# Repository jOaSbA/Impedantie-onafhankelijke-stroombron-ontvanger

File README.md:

"# Impedantie-onafhankelijke-stroombron-ontvanger"

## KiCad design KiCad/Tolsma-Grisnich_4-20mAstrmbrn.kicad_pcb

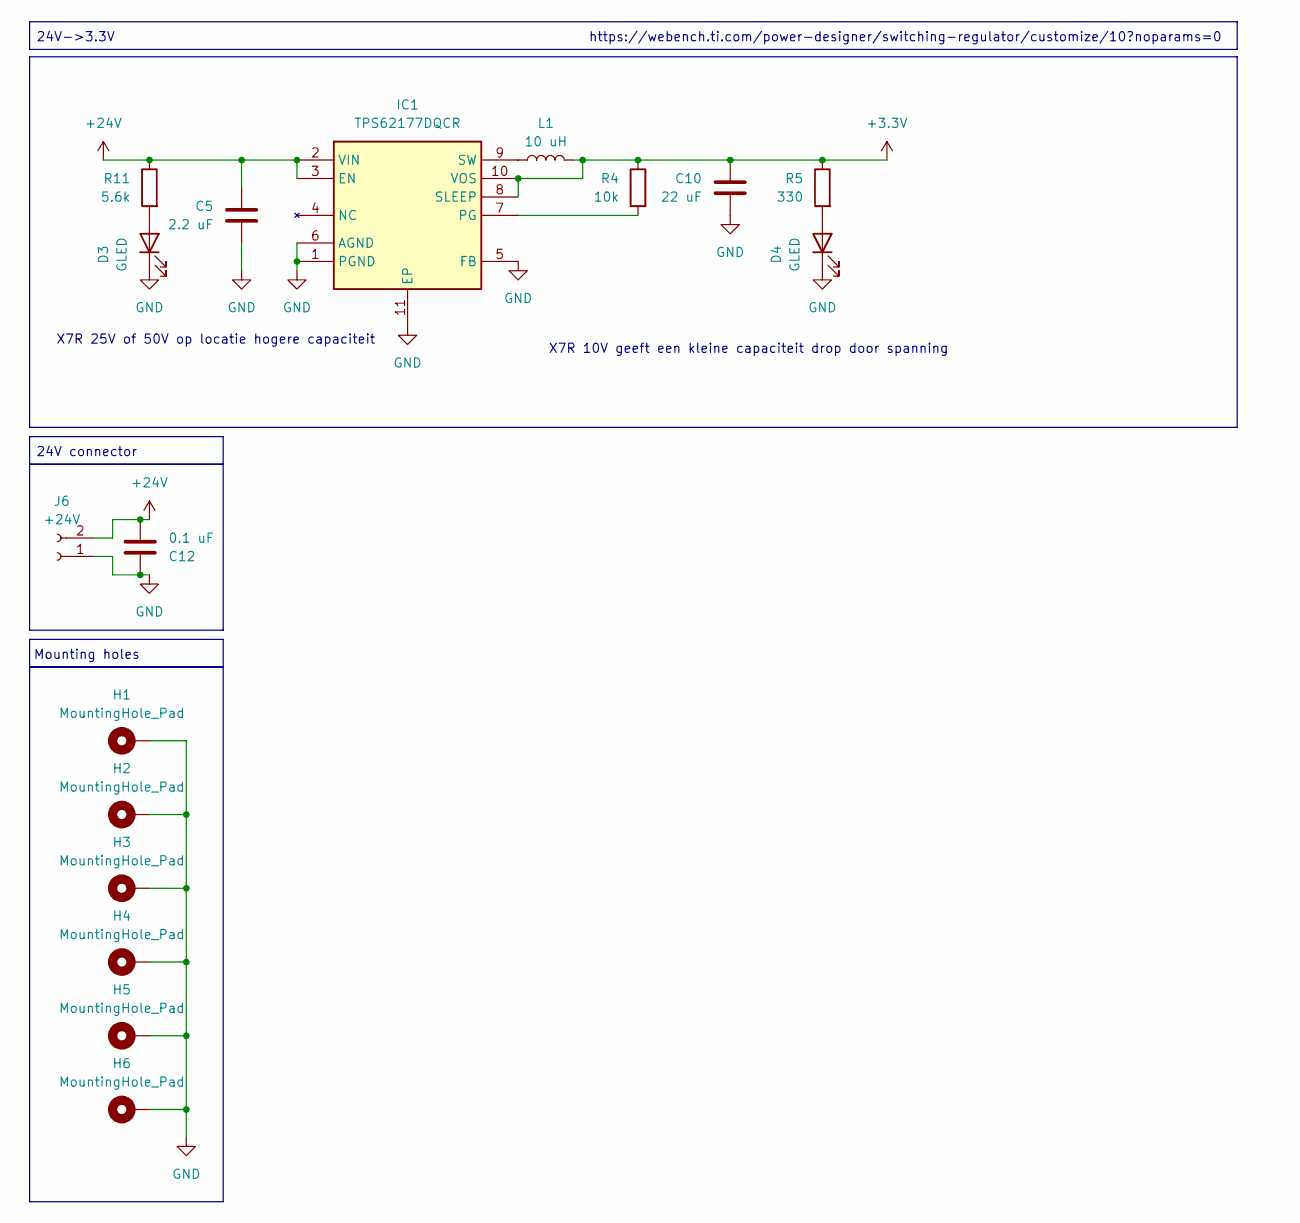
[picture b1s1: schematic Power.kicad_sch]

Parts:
C5: 2.2 uF; C_1206_3216Metric_Pad1.33x1.80mm_HandSolder
C10: 22 uF; C_1206_3216Metric_Pad1.33x1.80mm_HandSolder
C12: 0.1 uF; C_1206_3216Metric_Pad1.33x1.80mm_HandSolder
D3, D4: GLED; LED_0805_2012Metric_Pad1.15x1.40mm_HandSolder
H1, H2, H3, H4, H5, H6: MountingHole_Pad; MountingHole_3.2mm_M3_DIN965_Pad
IC1: TPS62177DQCR; SON50P200X300X80-11N; Mouser Part Number 595-TPS62177DQCR
J6: +24V; TerminalBlock_Xinya_XY308-2.54-2P_1x02_P2.54mm_Horizontal
L1: 10 uH; L_Wuerth_MAPI-3015
R4: 10k; R_1206_3216Metric_Pad1.30x1.75mm_HandSolder
R5: 330; R_1206_3216Metric_Pad1.30x1.75mm_HandSolder
R11: 5.6k; R_1206_3216Metric_Pad1.30x1.75mm_HandSolder

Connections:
+3.3V: C10.1, IC1.8 (SLEEP), IC1.10 (VOS), L1.2, R4.1, R5.1; also elsewhere on the board
+24V: C5.1, C12.2, IC1.2 (VIN), IC1.3 (EN), J6.2, R11.1; also elsewhere on the board
GND: C5.2, C10.2, C12.1, D3.1 (K), D4.1 (K), H1.1, H2.1, H3.1, H4.1, H5.1, H6.1, IC1.1 (PGND), IC1.5 (FB), IC1.6 (AGND), IC1.11 (EP), J6.1; also elsewhere on the board
unnamed: D3.2 (A), R11.2
unnamed: D4.2 (A), R5.2
unnamed: IC1.7 (PG), R4.2
unnamed: IC1.9 (SW), L1.1

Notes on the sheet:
X7R 10V geeft een kleine capaciteit drop door spanning
24V connector
24V->3.3V
Mounting holes
X7R 25V of 50V op locatie hogere capaciteit
https://webench.ti.com/power-designer/switching-regulator/customize/10?noparams=0

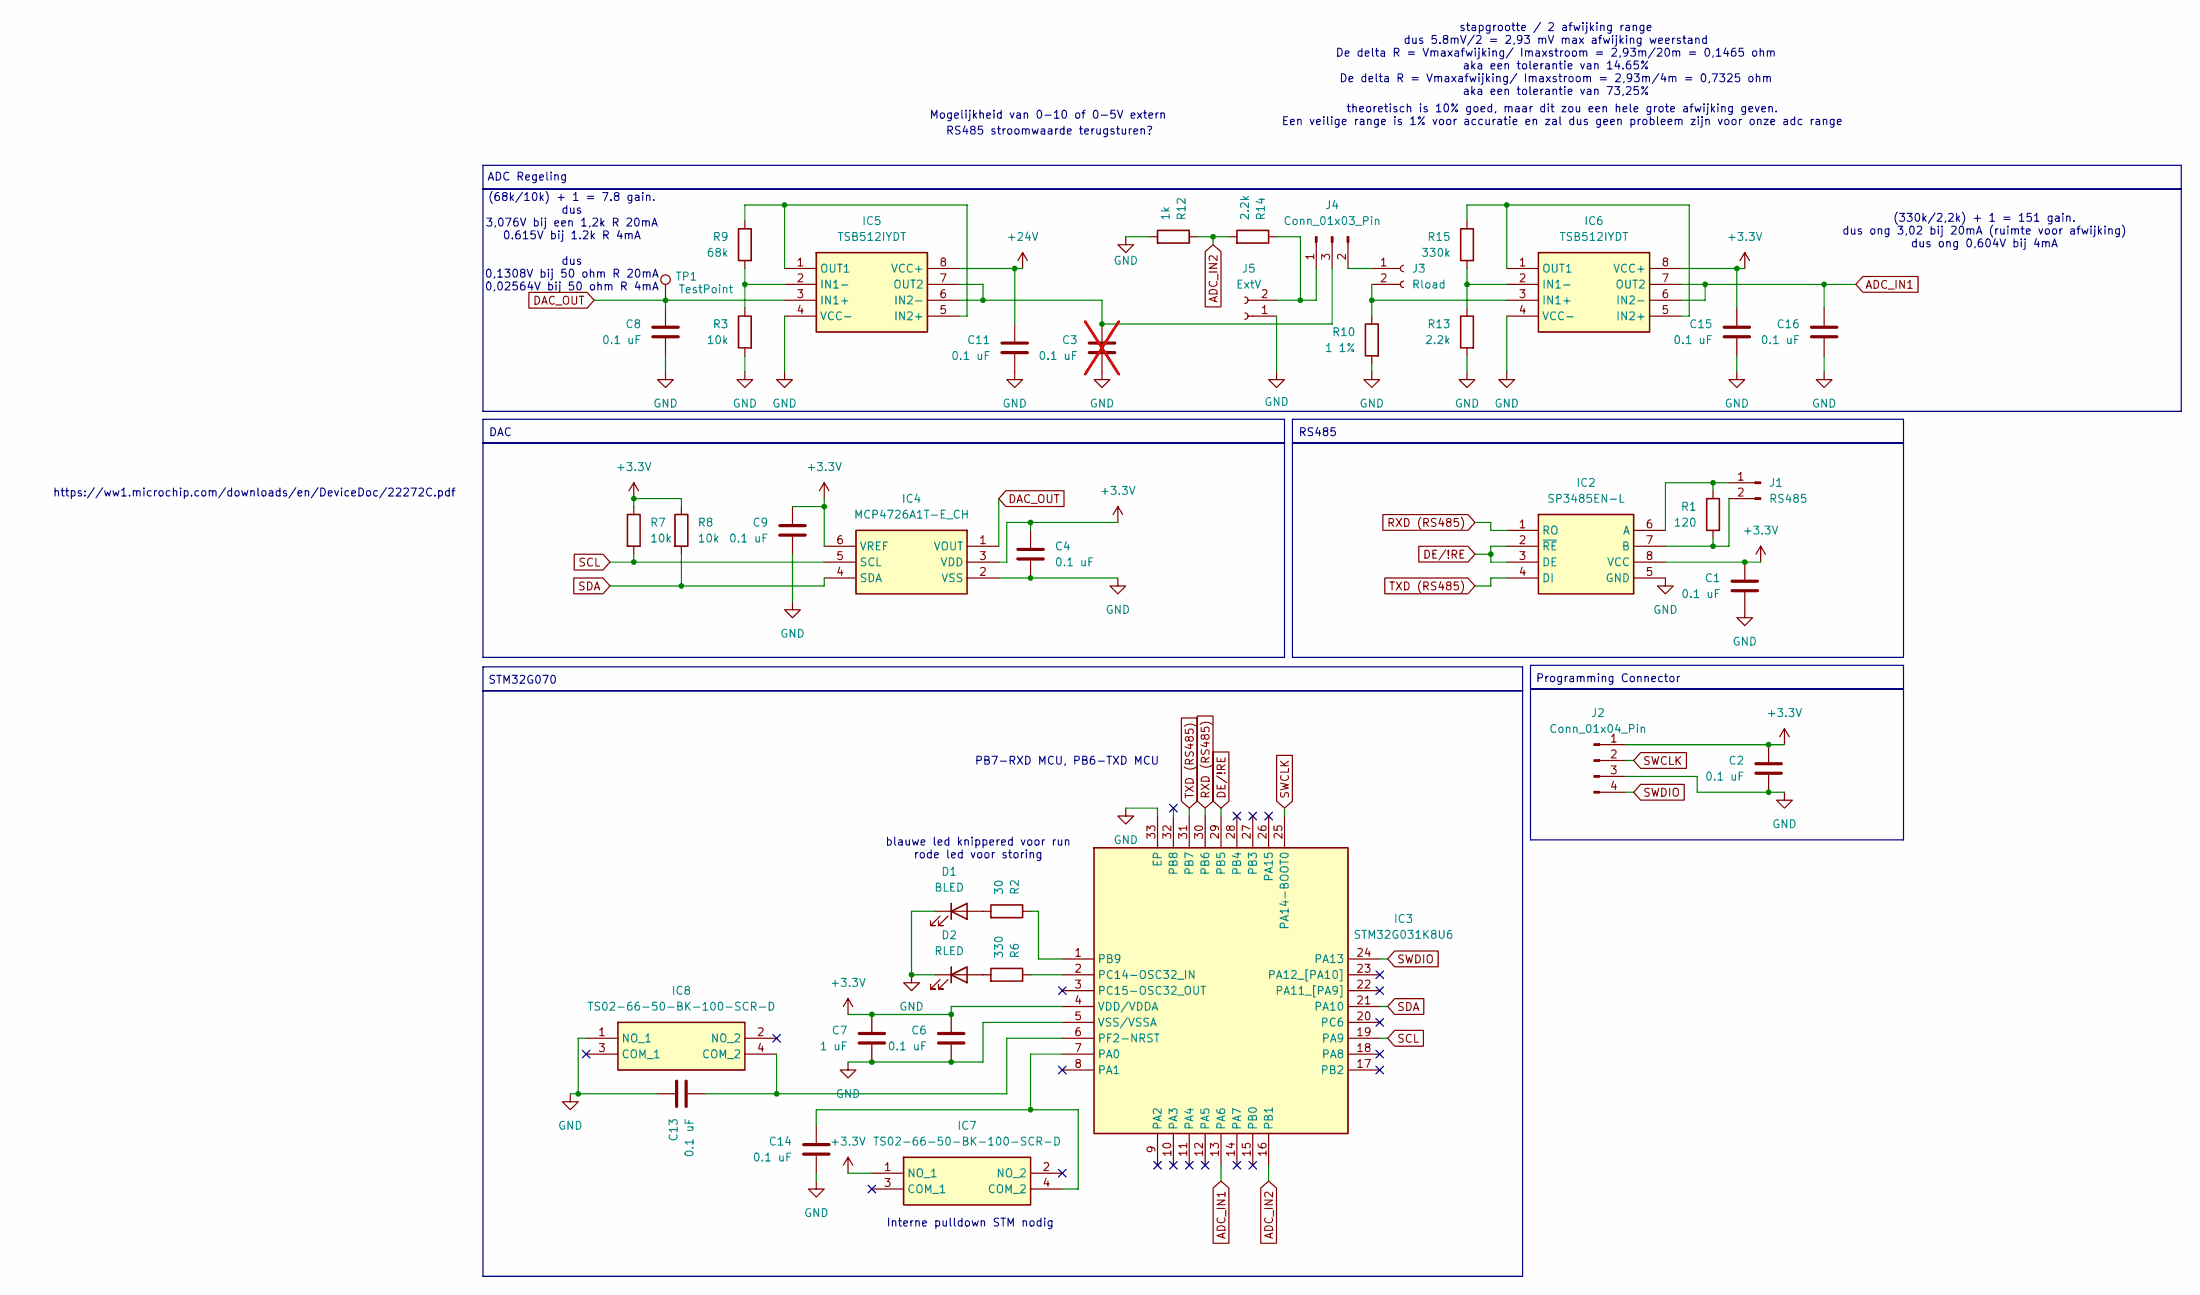
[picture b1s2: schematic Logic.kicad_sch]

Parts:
C1, C2, C4, C6, C8, C9, C11, C13, C14, C15, C16: 0.1 uF; C_1206_3216Metric_Pad1.33x1.80mm_HandSolder
C3: 0.1 uF; C_1206_3216Metric_Pad1.33x1.80mm_HandSolder; not fitted
C7: 1 uF; C_1206_3216Metric_Pad1.33x1.80mm_HandSolder
D1: BLED; LED_0805_2012Metric_Pad1.15x1.40mm_HandSolder
D2: RLED; LED_0805_2012Metric_Pad1.15x1.40mm_HandSolder
IC2: SP3485EN-L; SOIC127P600X175-8N; Manufacturer_Part_Number SP3485EN-L; Mouser Part Number 701-SP3485EN-L
IC3: STM32G031K8U6; QFN50P500X500X60-33N-D; Mouser Part Number 511-STM32G031K8U6
IC4: MCP4726A1T-E_CH; SOT95P270X145-6N; Manufacturer_Part_Number MCP4726A1T-E/CH; Mouser Part Number 579-MCP4726A1TECH
IC5, IC6: TSB512IYDT; SOIC127P600X175-8N; Manufacturer_Part_Number TSB512IYDT; Mouser Part Number 511-TSB512IYDT
IC7, IC8: TS02-66-50-BK-100-SCR-D; TS026650BK100SCRD; Mouser Part Number 179-TS026650BK100SCR
J1: RS485; TerminalBlock_Xinya_XY308-2.54-2P_1x02_P2.54mm_Horizontal
J2: Conn_01x04_Pin; PinHeader_1x04_P2.54mm_Vertical
J3: Rload; TerminalBlock_Xinya_XY308-2.54-2P_1x02_P2.54mm_Horizontal
J4: Conn_01x03_Pin; PinHeader_1x03_P2.54mm_Vertical
J5: ExtV; TerminalBlock_Xinya_XY308-2.54-2P_1x02_P2.54mm_Horizontal
R1: 120; R_1206_3216Metric_Pad1.30x1.75mm_HandSolder
R2: 30; R_1206_3216Metric_Pad1.30x1.75mm_HandSolder
R3, R7, R8: 10k; R_1206_3216Metric_Pad1.30x1.75mm_HandSolder
R6: 330; R_1206_3216Metric_Pad1.30x1.75mm_HandSolder
R9: 68k; R_1206_3216Metric_Pad1.30x1.75mm_HandSolder
R10: 1 1%; R_1206_3216Metric_Pad1.30x1.75mm_HandSolder
R12: 1k; R_1206_3216Metric_Pad1.30x1.75mm_HandSolder
R13, R14: 2.2k; R_1206_3216Metric_Pad1.30x1.75mm_HandSolder
R15: 330k; R_1206_3216Metric_Pad1.30x1.75mm_HandSolder
TP1: TestPoint; TestPoint_Pad_D1.5mm

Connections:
+3.3V: C1.1, C2.1, C4.1, C6.1, C7.1, C9.1, C15.1, IC2.8 (VCC), IC3.4 (VDD/VDDA), IC4.3 (VDD), IC4.6 (VREF), IC6.8 (VCC+), IC7.1 (NO_1), J2.1, R7.1, R8.1; also elsewhere on the board
+24V: C11.1, IC5.8 (VCC+); also elsewhere on the board
ADC_IN1: C16.1, IC3.13 (PA6), IC6.6 (IN2-), IC6.7 (OUT2)
ADC_IN2: IC3.16 (PB1), R12.1, R14.2
DAC_OUT: C8.1, IC4.1 (VOUT), IC5.3 (IN1+), TP1.1
DE/!RE: IC2.2 (~RE), IC2.3 (DE), IC3.29 (PB5)
GND: C1.2, C2.2, C3.2, C4.2, C6.2, C7.2, C8.2, C9.2, C11.2, C13.1, C14.2, C15.2, C16.2, D1.1 (K), D2.1 (K), IC2.5 (GND), IC3.5 (VSS/VSSA), IC3.33 (EP), IC4.2 (VSS), IC5.4 (VCC-), IC6.4 (VCC-), IC8.1 (NO_1), J2.3, J5.1, R3.2, R10.2, R12.2, R13.2; also elsewhere on the board
unnamed: D1.2 (A), R2.2
unnamed: D2.2 (A), R6.2
unnamed: IC2.6 (A), J1.1, R1.1
unnamed: IC2.7 (B), J1.2, R1.2
unnamed: C14.1, IC3.7 (PA0), IC7.4 (COM_2)
unnamed: IC3.1 (PB9), R2.1
unnamed: IC3.2 (PC14-OSC32_IN), R6.1
unnamed: C13.2, IC3.6 (PF2-NRST), IC8.4 (COM_2)
unnamed: IC5.2 (IN1-), R3.1, R9.2
unnamed: IC5.1 (OUT1), IC5.5 (IN2+), R9.1
unnamed: C3.1, IC5.6 (IN2-), IC5.7 (OUT2), J4.3
unnamed: IC6.3 (IN1+), J3.2, R10.1
unnamed: IC6.2 (IN1-), R13.1, R15.2
unnamed: IC6.1 (OUT1), IC6.5 (IN2+), R15.1
unnamed: J3.1, J4.2
unnamed: J4.1, J5.2, R14.1
RXD (RS485): IC2.1 (RO), IC3.30 (PB6)
SCL: IC3.19 (PA9), IC4.5 (SCL), R7.2
SDA: IC3.21 (PA10), IC4.4 (SDA), R8.2
SWCLK: IC3.25 (PA14-BOOT0), J2.2
SWDIO: IC3.24 (PA13), J2.4
TXD (RS485): IC2.4 (DI), IC3.31 (PB7)

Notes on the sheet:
theoretisch is 10% goed, maar dit zou een hele grote afwijking geven. Een veilige range is 1% voor accuratie en zal dus geen probleem zijn voor onze adc range
(68k/10k) + 1 = 7.8 gain. dus 3,076V bij een 1,2k R 20mA 0.615V bij 1.2k R 4mA dus 0,1308V bij 50 ohm R 20mA 0,02564V bij 50 ohm R 4mA
ADC Regeling
Programming Connector
blauwe led knippered voor run rode led voor storing
RS485 stroomwaarde terugsturen?
STM32G070
DAC
stapgrootte / 2 afwijking range dus 5.8mV/2 = 2,93 mV max afwijking weerstand De delta R = Vmaxafwijking/ Imaxstroom = 2,93m/20m = 0,1465 ohm aka een tolerantie van 14.65% De delta R = Vmaxafwijking/ Imaxstroom = 2,93m/4m = 0,7325 ohm aka een tolerantie van 73,25%
Mogelijkheid van 0-10 of 0-5V extern
(330k/2,2k) + 1 = 151 gain. dus ong 3,02 bij 20mA (ruimte voor afwijking) dus ong 0,604V bij 4mA
Interne pulldown STM nodig
https://ww1.microchip.com/downloads/en/DeviceDoc/22272C.pdf
PB7-RXD MCU, PB6-TXD MCU
RS485

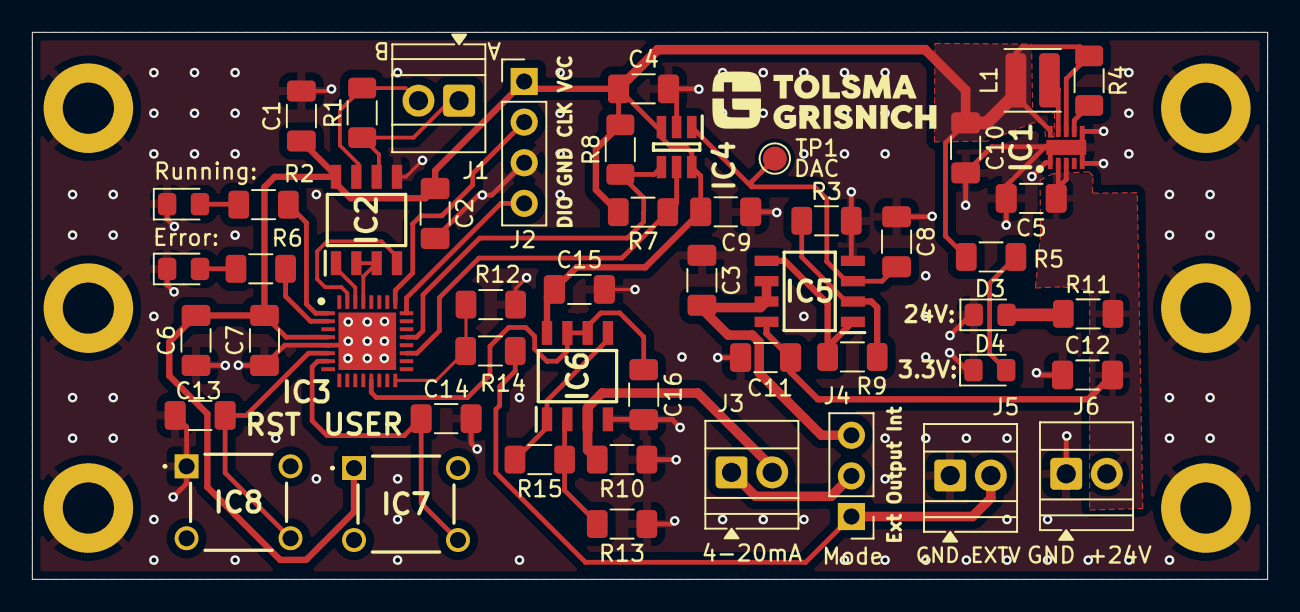
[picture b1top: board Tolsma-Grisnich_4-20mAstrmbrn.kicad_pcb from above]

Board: 2 copper layers, 77.2 x 34.2 mm, 57 parts (0 on the bottom side), 33 nets.

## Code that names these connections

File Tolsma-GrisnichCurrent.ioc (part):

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Mcu.Name=STM32G031K(4-6-8)Ux
Mcu.Package=UFQFPN32
Mcu.UserName=STM32G031K8Ux
PA0.Signal=GPIO_Input
PA10.Mode=I2C
PA10.Signal=I2C1_SDA
PA13.Mode=Serial_Wire
PA13.Signal=SYS_SWDIO
PA14-BOOT0.Mode=Serial_Wire
PA14-BOOT0.Signal=SYS_SWCLK
PA6.Mode=IN6
PA6.Signal=ADC1_IN6
PA9.Mode=I2C
PA9.Signal=I2C1_SCL
PB1.Mode=IN9
PB1.Signal=ADC1_IN9
PB5.GPIOParameters=GPIO_Label
PB5.GPIO_Label=DE/\!RE
PB5.Signal=GPIO_Output
PB6.Mode=Asynchronous
PB6.Signal=USART1_TX
PB7.Mode=Asynchronous
PB7.Signal=USART1_RX
PB9.Signal=GPIO_Output
PC14-OSC32_IN\ (PC14).Signal=GPIO_Output
RCC.HSE_VALUE=8000000
RCC.SYSCLKFreq_VALUE=16000000
board=custom

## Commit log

2026-01-06 DMA UART plus regeling in task
2026-01-07 PI regelaar toegevoegd voor stroomwaarde.
2026-01-07 DAC driver geschreven
2026-01-07 ADCtoStroom geschreven en bugfixes
2026-01-16 PI tuning, error is 10 lsb
2026-01-16 Kicad en image toegevoegd
2026-01-19 Mode wisseling, waardes gekalibreerd, werkende RS485, PI regeling verbeterd, led geimplementeerd, veiligere FreeRTOS operatie
